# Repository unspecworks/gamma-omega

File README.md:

# GAMMA OMEGA

A 36 Keys low-profile unibody ergonomic keyboard designed for portability and durability while still maintaining comfort.

*Portable? It may not be very compact, but you can still just toss it in your bag, right?*

## Variants
There are currently three variants of Gamma Omega in this repository, all using the same 36-key layout and spacing.

|   | Controller | Connection | PCB | Diodes | Roll-over | Switch | Built |
|-|-|-|-|-|-|-|-|
| [Original](/original/) | Raspberry Pi Pico | USB | Twin | 36 | NKRO 🥇 | Choc v1, v2 | :white_check_mark: | 
| [TC36K](/tc36k/) | Raspberry Pi Pico | USB | Mono | 0 | 6KRO 🥈 | Choc v1, v2[^1] | :white_check_mark: |
| [Hesse](/hesse/) | Nice!Nano v2/clone | USB/BLE | Mono | 0 | 4KRO 🥉 | Choc v1, v2 | :construction: |

[^1]: Choc v2 support since the TC36K v1.1.0.

The original and TC36K versions use the same case. The Hesse has a Bluetooth capable MCU controller and a slightly different case for the battery etc.

_See the `README.md` in each folder for more information._

## Technical Details

### Spacing

18 x 17mm (Choc spacing with a tighter grid)

### Dimensions

 - Length: 246mm
 -  Width: 119mm
 - Height: approx. 18mm 
   - feet to keycap (2mm height rubber feet and CFX choc v1 keycap)

### Weight

full built: approx. 301g (Original), 308g (TC36K)

### ergogen

The PCB was generated using [Ergogen](https://github.com/ergogen/ergogen), an ergonomic keyboard generator tool that simplifies the creation of custom keyboard layouts.

## Development Roadmap

- [ ] Support FDM/MJF version case w/ heat set insert method.
- [ ] Cherry MX ULP Switch Variant.

## SPECIAL THANKS 

[@GEIGEIGEIST](https://github.com/GEIGEIGEIST)
- This project was greatly inspired by his work. In particular, TOTEM. [TOTEM](https://github.com/GEIGEIGEIST/totem) is my favorite lo-pro split keyboard. Please check it out.​​​​​​​​​​​​​​​​

[Peter Cock](https://github.com/peterjc)
- Thanks for creating and contributing to the TC36k variant.

## Contributing

Contributions are welcome! Feel free to submit pull requests or open issues for any improvements or bug fixes.

The repository uses git-submodules for some footprints, it can easily be setup locally with:

```console
git clone --recurse-submodules https://github.com/unspecworks/gamma-omega.git
```

But I don't know much about modeling and PCB design.

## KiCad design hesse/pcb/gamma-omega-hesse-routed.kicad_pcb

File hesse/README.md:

# Gamma-Omega Hesse - BlueTooth mono PCB without diodes

## Quick Links
- [3D Printable Case](cases/) (which are *different* to the original Gamma Omega and TC36K):
- [PCB](pcb/) including the Gerbers ZIP file for getting the PCB fabricated at JLCPLC or similar,
  and BOM & position files which might work for assembly with the hot-swap sockets (untested as the
  parts were not available).
- [Ergogen Configuration](ergogen/README.md) 
- Firmware (which is *different* to the original Gamma Omega and the TC36K):
    - [Hesse ZMK Firmware](https://github.com/peterjc/zmk-keyboard-graph-theory/tree/main/boards/shields/hesse)
- [Build Guide](BUILD_GUIDE.md)

## Photos

Pending, but it looks like the original Gamma Omega - the key placement, PCB outline
and case outline remain the same. However the reset button is now on the top edge along
from the USB connector.

## PCB design

This iteration of the Gamma Omega family of 36-key keyboards is the first wireless one
which supports BlueTooth, specifically BlueTooth Low Energy (BLE) using ZMK firmware.
This meant a change in the controller, as even through the Raspberry Pi Pico W boards
might work, their Bluetooth module is not yet supported in ZMK, and they are much more
battery hungry than the controllers typically used with ZMK.

In order to stick with a diode-free Graph Theory wiring design, I really wanted a
BlueTooth controller with built in LiPo battery charging *and* at least 26 GPIO pins
to follow the same partial *Tutte Coxeter graph* wiring as used in the
[Gamma Omega TC36K](../tc36k/README.md) with 6-key roll over.

Instead, this design uses a [Nice!Nano v2](https://nicekeyboards.com/nice-nano)
or the [SuperMini NRF52840](https://kriscables.com/supermini-nrf52840/) aka
[ProMicro NRF52840](https://www.nologo.tech/product/otherboard/NRF52840.html).
These have built in BlueTooth, LiPo battery charging, ZMK support, but "only"
21 GPIO pins. The compromise means using a bipartite girth 6 graph of 21
vertices and 36 edges, giving *only 4-key roll over*. This is the *Hesse
Configuration Incidence Graph*, also known as the [incidence graph of the
affine plane of order 3](https://houseofgraphs.org/graphs/44164).

It looks like the original Gamma Omega - the key placement, PCB outline and
case outline remain the same. However the case moves the reset button to the
top edge along from the USB connector, and internally adds a battery
compartment. ZMK deep sleep is used in lieu of a physical on/off switch.

## Credits

[triliu/Heawood42](https://github.com/triliu/Heawood42) - the first no-diode keyboard using graph theory (42 key split)

[triliu/JESK56](https://github.com/triliu/JESK56) - later no-diode 56 key monoblock keyboard using graph theory

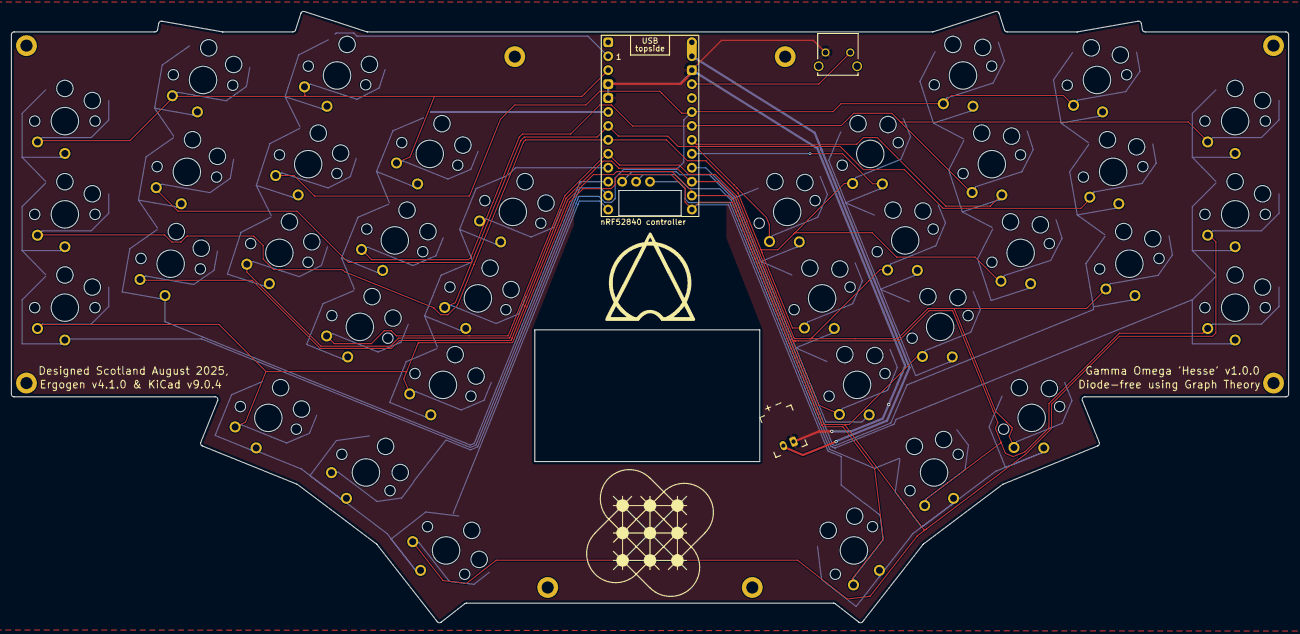
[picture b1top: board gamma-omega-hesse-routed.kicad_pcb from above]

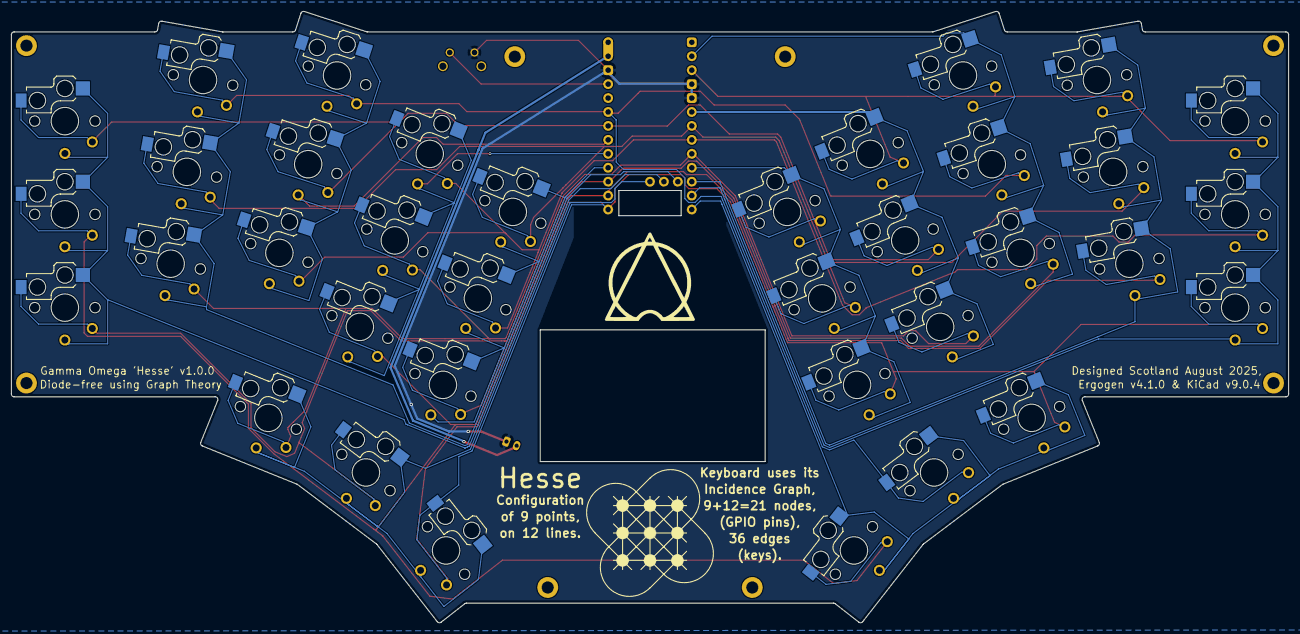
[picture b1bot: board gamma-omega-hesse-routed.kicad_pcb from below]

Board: 2 copper layers, 232.8 x 111.4 mm, 47 parts (36 on the bottom side), 24 nets.

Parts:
 nRF52840 controller: nice_nano_AH_USBup
H1, H2, H3, H4, H5, H6, H7, H8: mounting_hole_plated
JST1: battery_connector_jst_ph_2
RST1: reset_switch_1825027-8
S1, S2, S3, S4, S5, S6, S7, S8, S9, S10, S11, S12, S13, S14, S15, S16, S17, S18, S19, S20, S21, S22, S23, S24, S25, S26, S27, S28, S29, S30, S31, S32, S33, S34, S35, S36: switch_choc_v1_v2

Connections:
C1: nRF52840 controller.11, S1.1, S1.2, S2.1, S2.2, S3.1, S3.2
C2: nRF52840 controller.10, S4.1, S4.2, S5.1, S5.2, S6.1, S6.2
C3: nRF52840 controller.1, S7.1, S7.2, S8.1, S8.2, S9.1, S9.2
C4: nRF52840 controller.5, S10.1, S10.2, S11.1, S11.2, S12.1, S12.2
C5: nRF52840 controller.9, S13.1, S13.2, S14.1, S14.2, S15.1, S15.2
C6: nRF52840 controller.12, S16.1, S16.2, S17.1, S17.2, S18.1, S18.2
C7: nRF52840 controller.27, S34.1, S34.2, S35.1, S35.2, S36.1, S36.2
C8: nRF52840 controller.21, S31.1, S31.2, S32.1, S32.2, S33.1, S33.2
C9: nRF52840 controller.20, S28.1, S28.2, S29.1, S29.2, S30.1, S30.2
C10: nRF52840 controller.19, S25.1, S25.2, S26.1, S26.2, S27.1, S27.2
C11: nRF52840 controller.25, S22.1, S22.2, S23.1, S23.2, S24.1, S24.2
C12: nRF52840 controller.26, S19.1, S19.2, S20.1, S20.2, S21.1, S21.2
GND: nRF52840 controller.3, nRF52840 controller.4, nRF52840 controller.14, JST1.1, RST1.2
R1: nRF52840 controller.2, S3.1, S3.2, S6.1, S6.2, S9.1, S9.2, S12.1, S12.2
R2: nRF52840 controller.24, S1.1, S1.2, S13.1, S13.2, S16.1, S16.2, S36.1, S36.2
R3: nRF52840 controller.7, S2.1, S2.2, S25.1, S25.2, S30.1, S30.2, S32.1, S32.2
R4: nRF52840 controller.6, S5.1, S5.2, S14.1, S14.2, S23.1, S23.2, S33.1, S33.2
R5: nRF52840 controller.23, S4.1, S4.2, S18.1, S18.2, S20.1, S20.2, S28.1, S28.2
R6: nRF52840 controller.22, S7.1, S7.2, S19.1, S19.2, S31.1, S31.2, S35.1, S35.2
R7: nRF52840 controller.17, S8.1, S8.2, S17.1, S17.2, S24.1, S24.2, S27.1, S27.2
R8: nRF52840 controller.8, S10.1, S10.2, S22.1, S22.2, S29.1, S29.2, S34.1, S34.2
R9: nRF52840 controller.18, S11.1, S11.2, S15.1, S15.2, S21.1, S21.2, S26.1, S26.2
RAW: nRF52840 controller.13, nRF52840 controller.29, JST1.2
RST: nRF52840 controller.15, RST1.1

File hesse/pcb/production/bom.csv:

Designator,Footprint,Quantity,Value,LCSC Part #
JST1,battery_connector_jst_ph_2,1,,C157932
RST1,reset_switch_1825027-8,1,,C266196
"S1, S10, S11, S12, S13, S14, S15, S16, S17, S18, S19, S2, S20, S21, S22, S23, S24, S25, S26, S27, S28, S29, S3, S30, S31, S32, S33, S34, S35, S36, S4, S5, S6, S7, S8, S9",switch_choc_v1_v2,36,,C5333465

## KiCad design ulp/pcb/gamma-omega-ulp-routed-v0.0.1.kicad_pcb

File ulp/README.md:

# Gamma-Omega ULP - Cherry MX Ultra Low Profile Switch variants

> [!WARNING]
> Work in progress.

*top origianl, bottom ulp*

## Quick Links
- [3D Printable Case](../cases/)
- [PCB](pcb/) 
- [Ergogen Configuration](ergogen/README.md) 
- Firmwares
    - [QMK/VIAL Implementation](firmwares/QMK/gamma_omega/)
    - [ZMK Firmware](https://github.com/unspecworks/zmk-config-gamma-omega)
- [Build Guide](BUILD_GUIDE.md)

## Case

Although this variant shares the same layout as the original and TC36k, it has its own dedicated case to fully leverage the advantages of ULP.
Despite the same layout, a different case and PCB are required.

And unlike the original version, it will be designed to be FDM printable.

## PCB Design

This variant is based on the Tutte-Coxeter graph routing of the TC36k and also uses a single mono PCB.
For more details, please refer to the [TC36k PCB](../tc36k/README.md) documentation.

## Prototype logs
### v0.0.1 
- The first prototype had an overall height of just 5mm.
- The 0.8mm PCB turned out to be unsuitable for heavy use due to its lack of rigidity.
- The PLA FDM case was too flexible and prone to bending, leading to typing issues in various scenarios.
- The wall near the MCU soldering area was likely too thin, and there wasn't enough space for the controller.
- To improve print quality, I tried printing the case at a 45-degree angle, but the thin structure and numerous overhangs resulted in poor-quality prints.
I plan to iterate on this design to find better printing strategies and structural improvements.

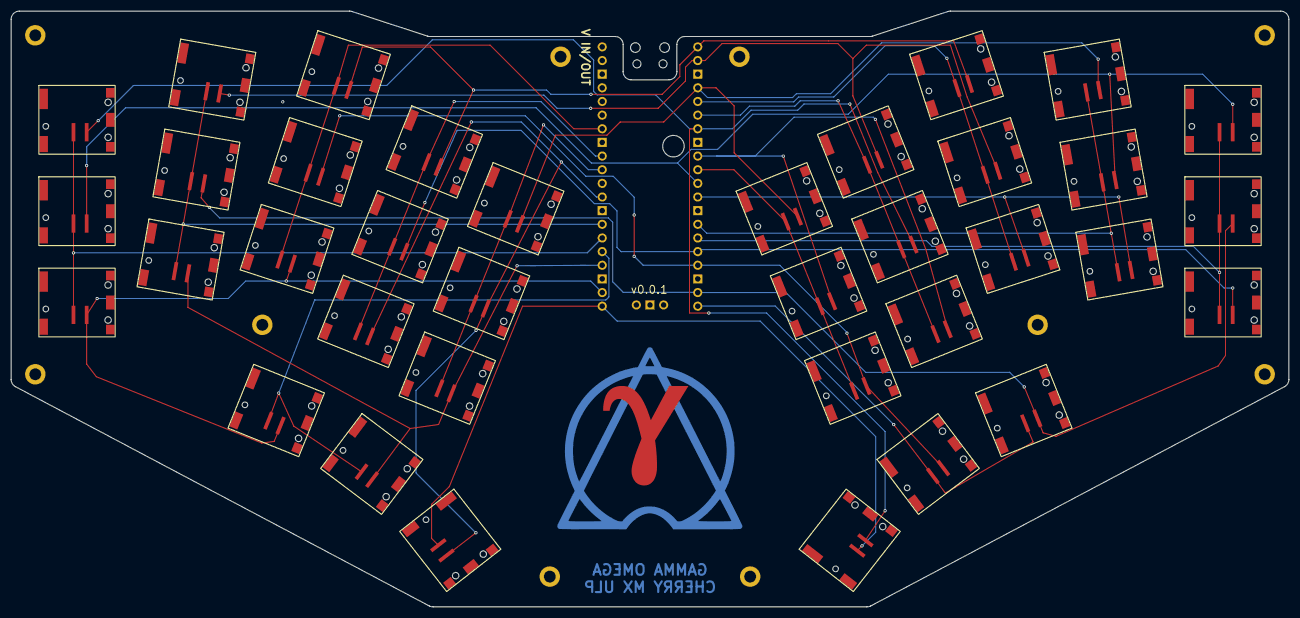
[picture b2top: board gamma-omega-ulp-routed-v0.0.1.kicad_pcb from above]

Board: 2 copper layers, 237.8 x 110.9 mm, 47 parts (0 on the bottom side), 27 nets.

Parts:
H1, H2, H3, H4, H5, H6, H7, H8, H9, H10: mounting_hole_plated
SW1, SW2, SW3, SW4, SW5, SW6, SW7, SW8, SW9, SW10, SW11, SW12, SW13, SW14, SW15, SW16, SW17, SW18, SW19, SW20, SW21, SW22, SW23, SW24, SW25, SW26, SW27, SW28, SW29, SW30, SW31, SW32, SW33, SW34, SW35, SW36: Cherry_ULP_SMD
_1: RPi_Pico_SMD_TH

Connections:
C1: SW19.1, SW20.1, SW21.1, _1.15
C2: SW22.1, SW23.1, SW24.1, _1.14
C3: SW25.1, SW26.1, SW27.1, _1.5
C4: SW28.1, SW29.1, SW30.1, _1.6
C5: SW31.1, SW32.1, SW33.1, _1.10
C6: SW13.1, SW14.1, SW15.1, _1.31
C7: SW10.1, SW11.1, SW12.1, _1.32
C8: SW7.1, SW8.1, SW9.1, _1.34
C9: SW34.1, SW35.1, _1.20
C10: SW4.1, SW5.1, SW6.1, _1.27
C11: SW16.1, SW17.1, _1.25
C12: SW1.1, SW2.1, SW3.1, _1.26
C13: SW18.1, SW36.1, _1.21
GND: _1.3, _1.8, _1.13, _1.18, _1.23, _1.28, _1.38
R1: SW11.2, SW19.2, _1.16
R2: SW2.2, SW21.2, SW23.2, _1.11
R3: SW22.2, SW25.2, _1.12
R4: SW6.2, SW26.2, SW30.2, _1.2
R5: SW28.2, SW32.2, _1.9
R6: SW15.2, SW24.2, SW33.2, _1.4
R7: SW10.2, SW14.2, SW18.2, _1.29
R8: SW9.2, SW12.2, SW27.2, _1.1
R9: SW8.2, SW31.2, SW35.2, _1.17
R10: SW5.2, SW20.2, SW34.2, _1.19
R11: SW4.2, SW13.2, SW17.2, _1.24
R12: SW1.2, SW7.2, SW16.2, _1.22
R13: SW3.2, SW29.2, SW36.2, _1.7

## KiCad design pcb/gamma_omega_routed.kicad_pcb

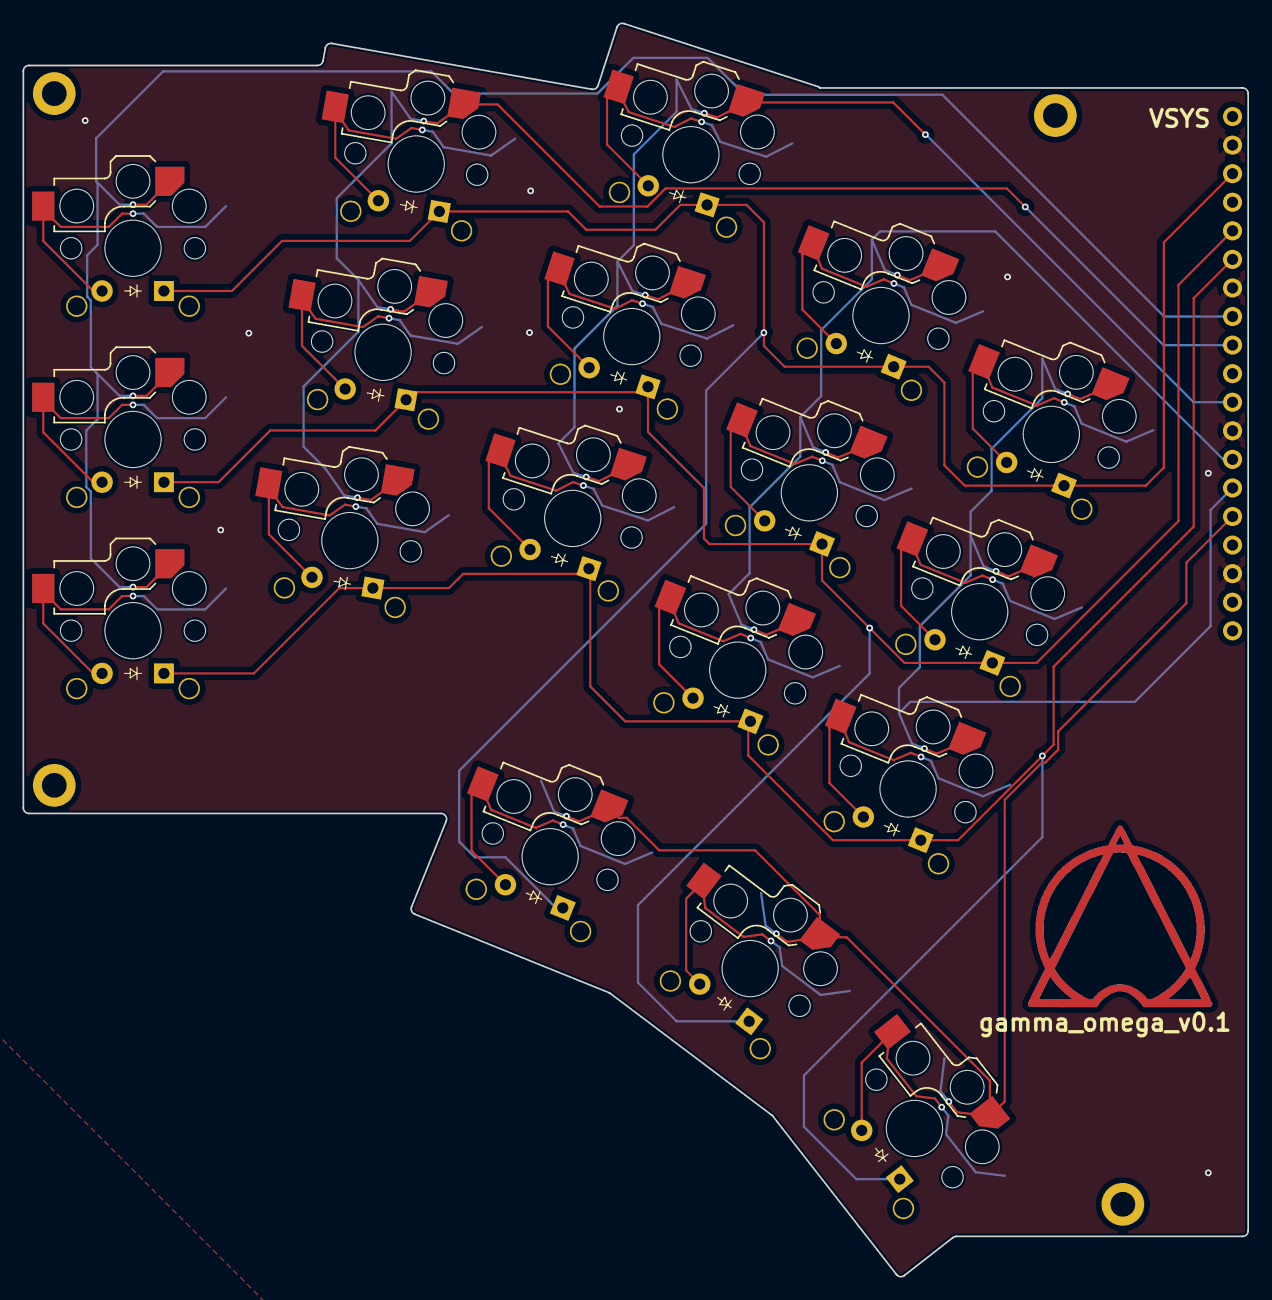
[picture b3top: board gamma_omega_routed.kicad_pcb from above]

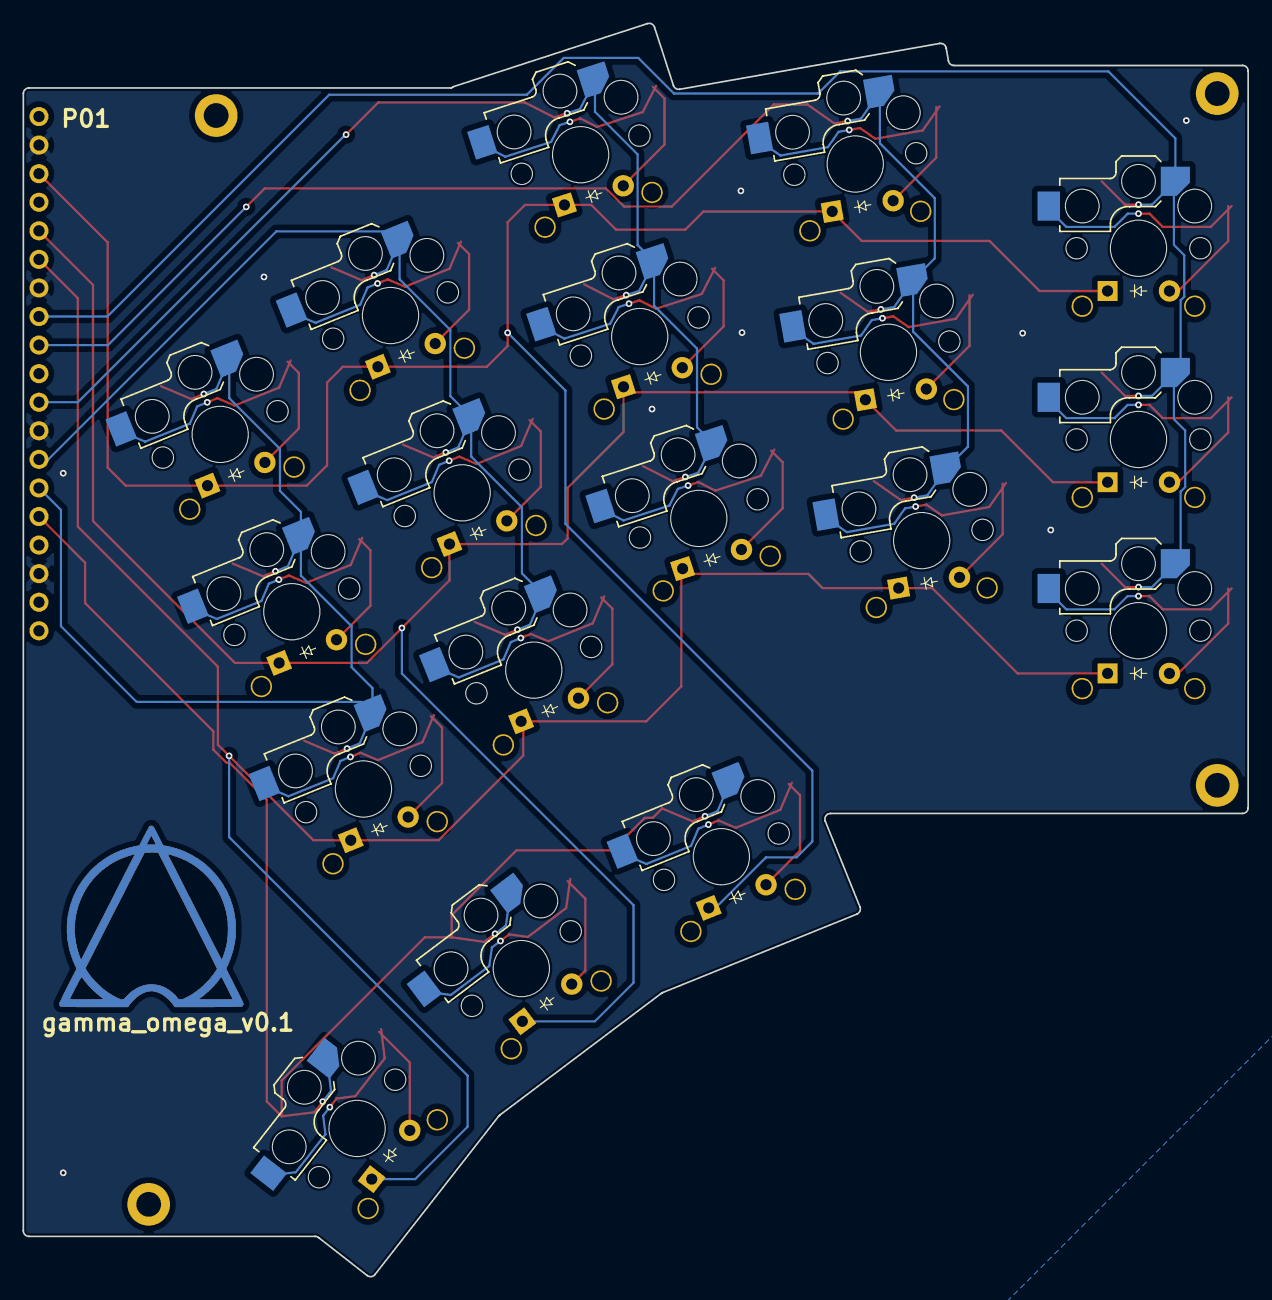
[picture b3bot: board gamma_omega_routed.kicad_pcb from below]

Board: 2 copper layers, 108.9 x 111.4 mm, 41 parts (18 on the bottom side), 28 nets.

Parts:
D1, D2, D3, D4, D5, D6, D7, D8, D9, D10, D11, D12, D13, D14, D15, D16, D17, D18: diode_tht_sod123
H1, H2, H3, H4: mounting_hole_plated
MCU1: nice_nano
S1, S2, S3, S4, S5, S6, S7, S8, S9, S10, S11, S12, S13, S14, S15, S16, S17, S18: switch_choc_v1_v2

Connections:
C0: MCU1.9, S1.1, S2.1, S3.1
C1: MCU1.10, S4.1, S5.1, S6.1
C2: MCU1.12, S7.1, S8.1, S9.1
C3: MCU1.14, S10.1, S11.1, S12.1
C4: MCU1.15, S13.1, S14.1, S15.1
C5: MCU1.16, S16.1, S17.1, S18.1
GND: MCU1.3, MCU1.8, MCU1.13, MCU1.18
R0: D3.1, D6.1, D9.1, D12.1, D15.1, D16.1, MCU1.4
R1: D2.1, D5.1, D8.1, D11.1, D14.1, D17.1, MCU1.6
R2: D1.1, D4.1, D7.1, D10.1, D13.1, D18.1, MCU1.7
S1: D3.2, S3.2
S2: D2.2, S2.2
S3: D1.2, S1.2
S4: D6.2, S6.2
S5: D5.2, S5.2
S6: D4.2, S4.2
S7: D9.2, S9.2
S8: D8.2, S8.2
S9: D7.2, S7.2
S10: D12.2, S12.2
S11: D11.2, S11.2
S12: D10.2, S10.2
S13: D15.2, S15.2
S14: D14.2, S14.2
S15: D13.2, S13.2
S16: D16.2, S16.2
S17: D17.2, S17.2
S18: D18.2, S18.2

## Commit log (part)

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2025-04-20 first init
2025-04-23 Improved top case model
2025-04-23 Add gerber file and update docs.
2025-04-24 Improve the clarity of the spacing.
2025-04-24 added about pin headers
2025-04-24 fix typo
2025-04-24 add showcase images. almost done for now.
2025-05-03 added zmk firmware link
2025-06-11 Document importance of boot button placement on RP2040 controller
    The PNG image was cropped from the Ali Express listing for the "black" board.
    The boot button circled in red.
    The "green" and "purple" boards on this listing have different button placement.
    The "Lite" versions too, plus they are narrower than the Pi Pico standard.
2025-06-11 Fix board alt-text
2025-06-11 Link to diagram, rather than show in-line
2025-06-12 Don't use infused-kim footprints directly (3D refs only)
2025-06-17 Drop diodes; Assign Tutte-Coxeter based sparse scanning matrix wiring
    Using C1 to C13 for the scanning columns (ten sets of three for the
    physical columns in the main zone, and three sets of two for thumbs),
    and R1 to R13 for the scanning 'rows' which do not match the physical
    rows at all.
    Note using one-based counting as per my figures on the blog post:
    https://astrobeano.blogspot.com/2025/05/ergo-mech-keyboard-wiring-using-tutte-coxeter-graph.html
2025-06-17 Move C11 above R13 to simplify the R13 to thumb row-scan trace
2025-06-17 This will not be a reversible PCB, so simpler choc footprints
2025-06-17 Allow for soldering switches OR hotswap; drop choc v2
2025-06-17 Restore missing GP21 silkscreen label
2025-06-17 Back traces in KiCad
    The R6 trace to column C6 is making lots of row detours.
    This wasn't very obvious on my paper sketch.
2025-06-17 Put hotswap and Pico controller on front to match switch net layout
    This means the PCB 'front' will be face down on the table once
    assembled - with the Raspberry Pi 2040 chip also facing the table.
2025-06-17 Adding hotswap/soldering traces and core column traces
    A few of the left-hand traces are deliberately different to allow
    adding a scan-row trace on the same side.
2025-06-17 Add the partial Tutte-Coxeter Graph to the silkscreen
    This is on both front and back.
2025-06-17 Link to firmware for 36 edges with Tutte-Coxeter graph
    Link to tutte_coxeter_36k firmware using the Tutte-Coxeter graph
    defined sparse 13x13 scanning matrix with only 36 entries, and
    the currently assigned GPIO pins.
2025-06-17 Starting work on a no-diode mono-PCB layout using Graph Theory
    See issue #1 and https://astrobeano.blogspot.com/2025/05/ergo-mech-keyboard-wiring-using-tutte-coxeter-graph.html
    The plan is to design an alternative larger single PCB compatible with the original Gamma-Omega case.
    This will use the same class of 26 GPIO microcontroller and a 26 of 30 vertex subset of the bipartite Tutte-Coxeter graph to control 36 keys (graph edges) within a sparse 13x13 virtual scanning matri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
2025-06-17 Remove commented-out 4th thumb key
2025-06-17 Change pinky & ring column wiring to account for stagger
    There isn't really enough space to reach these outer columns
    round the top (as in my original sketch solution). Taking the
    column stagger into account, easier from the bottom.
2025-06-17 Set KiCad output folder for Gerbers
2025-06-17 Fix R2, C1 left ring, C10 right pinky etc trace margins
    This was a relic of an early copy-paste positioning.
2025-06-18 Bundle third-party Raspberry Pi Pico footprint
    This is from Ergogen pull request 144 by Vladimir Andral in Dec 2024
    (GitHub user VladAndral), based on a first draft by Thomas Andersen
    in Feb 2022 (GitHub user TTA777) here:
    https://github.com/TTA777/ergogen/commit/817e013d4880876b9fd51707de45c7b36a1b5077
    This is therefore (like Ergogen) under the MIT License. If this
    or something like it is added to Ergogen, we can drop this.
2025-06-23 Define boot button cut-out
2025-06-23 Draw TC36K silkscreen graph art as an Ergogen footprint
    Currently generating this in Python, but should be able to do it all in JS.
    Label placement etc assumes 26 nodes (36 edges), looks OK with all 30.
    Would need tweaking for a pretty version with 28 nodes etc.
2025-06-26 Initial PCB from Ergogen v4.1.0, via KiCad v9.0.2
    ❯ ergogen tc36k/ergogen && cp output/pcbs/gamma-omega-tc36k.kicad_pcb tc36k/pcb/gamma-omega-tc36k-routed.kicad_pcb
    Ergogen v4.1.0 CLI
    Analyzing folder...
    Interpreting format: YAML
    Preprocessing input...
    Checking compatibility...
2025-06-26 Traces and ground plane in KiCad v9.0.2
    This was the result of a lot of iterative work, which does not
    work well in version control (too much floating point noise).
    This passes the Design Rules Checker except for a warning from
    each ceoloide footprint not being in the library, a warning for
    the USB cut-out clipping the controller footprint (deliberate),
    and 2 errors about not enough spokes for ground plane zones
2025-06-27 Update footprints symlink following repo reorganization
2025-06-27 Typo
2025-06-27 Assign LCSC part number C9900009224 for CPG135001S30 choc hotswap sockets.
    Using the KiCad JLCPLC Tools plugin for this. Currently out of stock.
    Alternative LCSC C5333465 more expensive and effectively out of stock too.
2025-06-27 Assign LCSC part number C5333465 for CPG135001S30 choc hotswap sockets.
    More expensive but can actually pre-order this part.
2025-07-03 Document tc36k/pcb/production/ folder
2025-07-04 The hot-swap sockets are optional, can solder switches directly
2025-07-18 Clarify insert nuts for case
    Closes #12.
2025-07-18 Flashing TC36k firmware
2025-07-18 Fix italics etc
2025-07-19 Test CAPS LOCK as a diagnostic step
2025-07-20 Keep diode away.
2025-07-29 Update TC36k firmware link; start hotswap instructions
2025-07-29 Illustrate hotswap circuit-testing (TC36k PCB)
2025-07-29 Show pre-assembled TC36k PCB with the PR2040 controller & headers
2025-07-29 Clarify testing steps
2025-07-29 Show installed nuts, and PCB in case
2025-07-29 Fix image filenames
2025-07-29 Only need one side USB photo
2025-07-31 Small photos in original Gamma Omega README
    Will help with multiple keyboards in the repo.
2025-08-01 Remove WIP warning
2025-08-01 Replace WIP column with completed
2025-08-01 Big K
2025-08-01 Added weight things for TC36K
    when the ULP version are merged, move this info into each stand section.
2025-08-30 fix typos in tc36k_logo.py
2025-09-01 Renamed repo
2025-09-16 Show bottom case in KiCad (via the controller footprint)
2025-09-16 Correct orientation of the choc hotswap 3D models in KiCad
2025-09-18 Added covered bottom case.
    - This is identical to Pull Request #24, but the STEP file has been re-exported using Fusion 360 instead of FreeCAD due to too much increased file size.
2025-09-22 Setup Ergogen folder
2025-09-22 Improve visual alignment of radio keepout with battery cutout
2025-09-22 Swap to Nice Nano footprint to do the tighter wiring
    Can swap back or add the Supermini nRF52840 pins later (within the
    Nice Nano radio keepout).
2025-09-22 Move the reset button more centrally
    This is tighter to the screw hole, less tucked in the case corner.
2025-09-22 Silk screen version of the Hesse Configuration (12 lines & 9 points)
2025-09-22 Support both choc v1 & v2 switches
    This fixes an oversight in the TC36K design settings.
2025-09-22 Update ceoloide footprints for keep-out support
2025-09-22 Add name and version in corner of PCB
2025-09-22 Switch first draft wiring (based on sorted matrix)
2025-09-22 Drop Molex battery option, rotate JST, enlarge battery cutout
2025-09-22 Right angle reset switch 1825027-8
2025-09-22 Centre row wiring on pad
2025-09-22 Vertically center col wiring on hole
2025-09-22 Pre-wire the hotswap pads & direct solder holes (on back)
2025-09-22 Bigger battery...
2025-09-22 Gamma Omega 'Hesse' is a better name than placeholder 'GT36K'.
    The underlying graph of the affine plane of order 3 is also known as the
    Hesse Configuration <https://en.wikipedia.org/wiki/Hesse_configuration>.
    So what we are using could reasonably be called the 'Hesse Configuration
    Incidence Graph'. A visually pleasing drawing of this is tricky, but the
    Hesse Configuration Graph would work as a silk screen illustration.
2025-09-22 Switch to ceoloide/mcu_supermini_nrf52840 footprint
    The 'incidence graph of the affine plane of order 3' wiring will use
    the bipartite 21 vertex split as 12 physical columns (including thumbs)
    and 9 scanning rows. Thus placeholder wiring net entries C1 to C12,
    and R1 to R9.
2025-09-22 Move battery slot 3mm down to match bottom edge of current void in case
    Top case will need cross-bar moved up for the desired battery placement.
2025-09-22 Starting work on a bluetooth variant, GT36K.
2025-09-22 Move Supermini NRF52840 up 9mm to edge of PCB
    Verified pin coordinates versus TC36K PCB.
    Note this footprint does not include the top two pins for the battery connection...
2025-09-22 Link to the excellent Kris Cables page on the SuperMini NRF52840
2025-09-22 Use KiCad default trace width of 0.2, not 0.25
2025-09-22 First draft of Hesse build guide
2025-09-22 Add date and version of tools used in corner of PCB
2025-09-22 Add battery cut-out, eg 3.7v 110mAh 301230
    That is a commonly used size of 3mm thickness, and 12mm by 30mm footprint.
    This placement aims to leave a keepout at the bottom of the controller for
    the bluetooth signal, but above the case taper and structural cross beam.
    Will still need to adust the top and or bottom case for this...
    This location should leave enough space either side of the battery space
    for traces similar to the layout used on the TC36K.
2025-09-22 Describe Hesse Configuration Graph on back (only)
2025-09-22 Add JST battery socket (will move battery slot over)
    This is on the left, even though the RAW pin is on the right, because
    that turned out to be easier to route the traces to with my draft wiring
    layout.
2025-09-22 Remove Tutte-Coxeter Graph silkscreen art (using different graph here)
2025-09-22 Link to hesse-nice_nano_v2-zmk.uf2
2025-09-22 typos
2025-09-23 Polish routing at nice nano footprint; mark Supermini nRF52840 hole trio
2025-09-23 Use PCM_marbastlib-xp-promicroish:nice_nano_AH_USBup footprint
2025-09-23 Remove duplicated automated traces from Ergogen
2025-09-24 Move Hesse reset switch 1mm in (for case clearance)
2025-09-30 Enable larger choc v1 or v2 center hole for TC36K in Ergogen
    The stabiliser doesn't seem to fully support the dual
    hotswap or soldering footprints, and is rare on recent
    choc v2 switches anyway - so don't add that. See:
    https://github.com/ceoloide/ergogen-footprints/issues/64
2025-09-30 Update text to TC36K v1.1.0, move traces by centre hole, shorten traces
    Add reset label, restore ground plane
2025-10-01 Update README.md
    Now TC36k supports Choc v2 as well. refer #27
2025-10-01 Use right column for note
2025-10-06 Use KiCad's 3D model for JST PH 2.0 battery connector
2025-10-06 Top case for 'Hesse' Bluetooth variant (joint effort)
    Based on the original top case with the following changes:
    * Moved rib beams for new battery compartment.
    * Moved beam for new reset button.
    * New hole for reset button.
    * Head room for reset switch.
    * LED funnels in Hesse top-case (0.9mm thick skin) inspired by
2025-10-07 Fix top case offset for KiCad 3D model usage
2025-10-07 Hesse Gerbers ZIP, BOM & positions etc from KiCad Fabrication-Toolkit
    See https://github.com/bennymeg/Fabrication-Toolkit
    Positions not validated - unable to pre-order the hotswap sockets
    and so JLCPLC would not let me proceed with an assembly order.
2025-10-29 Gamma-Omega TC36K Quick Links
    Make this page structure follow the original's README.
    Hopefully the firmware being different is more obvious now.
2025-10-29 Keep consise summary in title
2025-10-29 Emphasize firmware name
